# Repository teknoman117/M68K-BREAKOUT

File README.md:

# M68K-BUS-VOLTAGE-CONVERTER

A breakout board for the MC68010 that drops the 5V TTL bus voltages to a 3.3V CMOS bus you can use with an FPGA.

Licensed under CC-BY-SA 4.0

## Pins

All MC68010 signals are converted with the exception of the MC6800 peripheral interface pins. VMA and E are left floating, and VMA is tied to 5V through a 2K2 resistor, which does prevent the use of autovectored interrupts. However, considering it's attached to an FPGA, a proper interrupt controller is a simple thing to add.

The RESET and HALT pins are able to be driven by the M68K itself, or by the FPGA. There are "RESET_OUT" and "HALT_OUT" pins which output the converted state of the pins, and "RESET_IN" and "HALT_IN" which connect to an inverter with open-collector outputs, allowing the FPGA to drive them low.

### Assembled

### PCB

### Schematic

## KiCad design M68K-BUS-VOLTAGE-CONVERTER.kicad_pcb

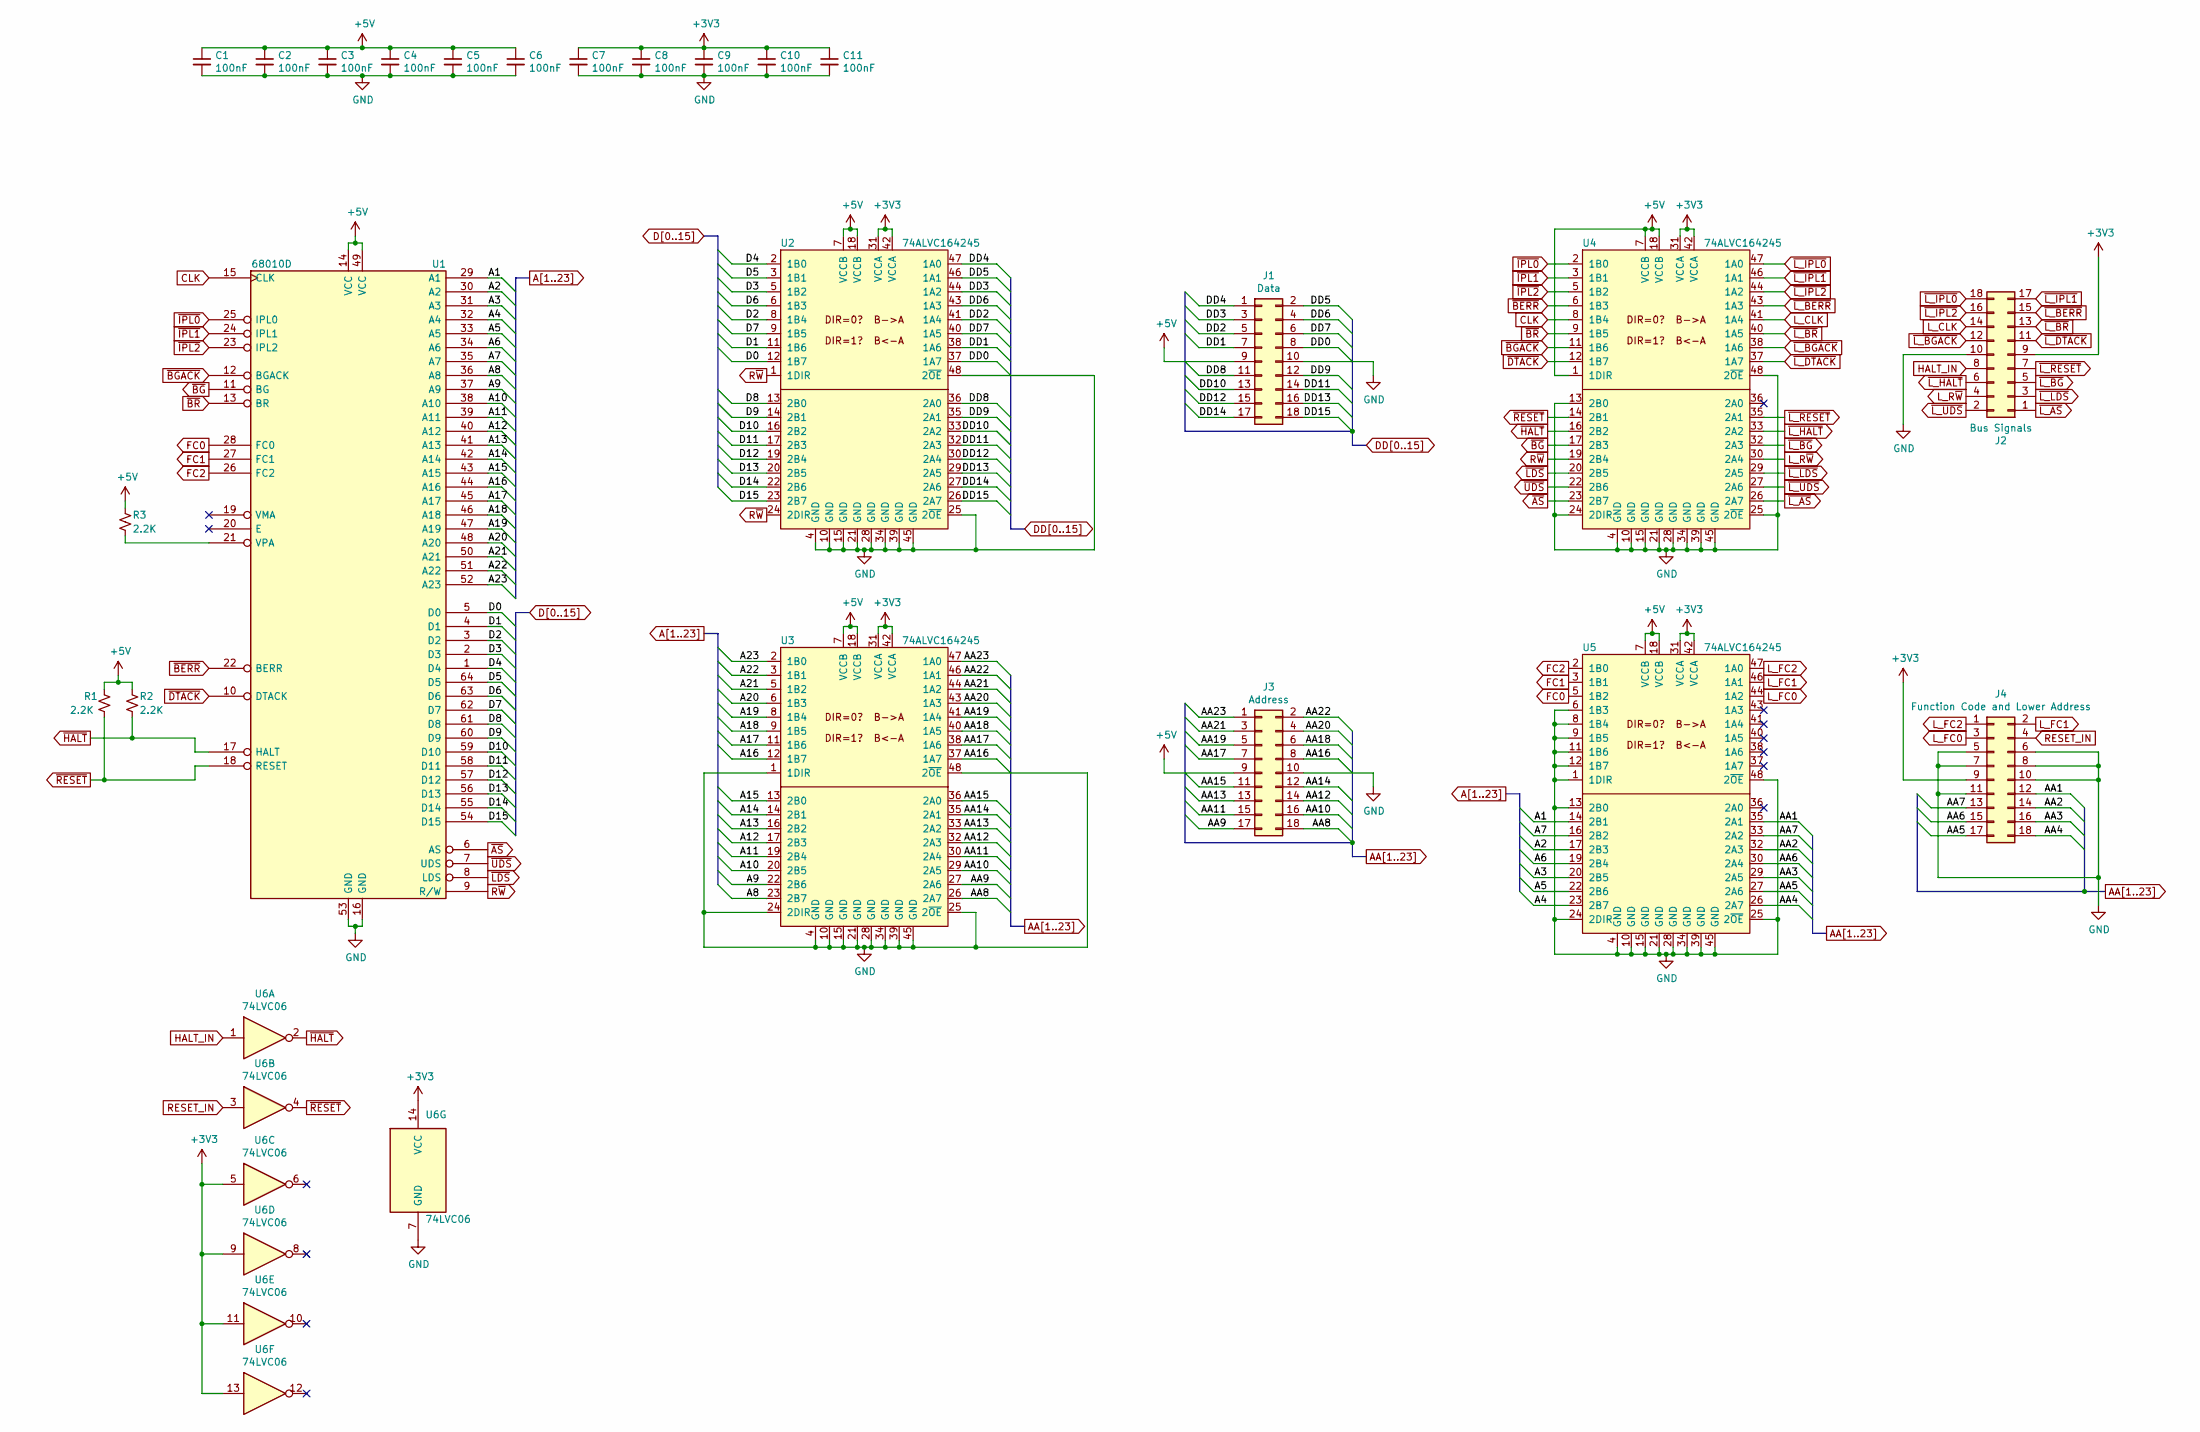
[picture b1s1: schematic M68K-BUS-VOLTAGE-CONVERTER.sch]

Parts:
C1, C2, C3, C4, C5, C6, C7, C8, C9, C10, C11: 100nF; C_0603_1608Metric_Pad1.08x0.95mm_HandSolder
J1: Data; PinHeader_2x09_P2.00mm_Vertical
J2: Bus Signals; PinHeader_2x09_P2.00mm_Vertical
J3: Address; PinHeader_2x09_P2.00mm_Vertical
J4: Function Code and Lower Address; PinHeader_2x09_P2.00mm_Vertical
R1, R2, R3: 2.2K; R_0603_1608Metric_Pad0.98x0.95mm_HandSolder
U1: 68010D; DIP-64_W22.86mm_Socket
U2, U3, U4, U5: 74ALVC164245; TSSOP-48_6.1x12.5mm_P0.5mm
U6: 74LVC06; SOIC-14_3.9x8.7mm_P1.27mm

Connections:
+3V3: C7.1, C8.1, C9.1, C10.1, C11.1, J2.9, J4.9, U2.31 (VCCA), U2.42 (VCCA), U3.31 (VCCA), U3.42 (VCCA), U4.31 (VCCA), U4.42 (VCCA), U5.31 (VCCA), U5.42 (VCCA), U6.5, U6.9, U6.11, U6.13, U6.14 (VCC)
+5V: C1.1, C2.1, C3.1, C4.1, C5.1, C6.1, J1.9, J3.9, R1.1, R2.1, R3.1, U1.14 (VCC), U1.49 (VCC), U2.7 (VCCB), U2.18 (VCCB), U3.7 (VCCB), U3.18 (VCCB), U4.1 (1DIR), U4.7 (VCCB), U4.18 (VCCB), U5.7 (VCCB), U5.18 (VCCB)
A1: U1.29 (A1), U5.14 (2B1)
A2: U1.30 (A2), U5.17 (2B3)
A3: U1.31 (A3), U5.20 (2B5)
A4: U1.32 (A4), U5.23 (2B7)
A5: U1.33 (A5), U5.22 (2B6)
A6: U1.34 (A6), U5.19 (2B4)
A7: U1.35 (A7), U5.16 (2B2)
A8: U1.36 (A8), U3.23 (2B7)
A9: U1.37 (A9), U3.22 (2B6)
A10: U1.38 (A10), U3.20 (2B5)
A11: U1.39 (A11), U3.19 (2B4)
A12: U1.40 (A12), U3.17 (2B3)
A13: U1.41 (A13), U3.16 (2B2)
A14: U1.42 (A14), U3.14 (2B1)
A15: U1.43 (A15), U3.13 (2B0)
A16: U1.44 (A16), U3.12 (1B7)
A17: U1.45 (A17), U3.11 (1B6)
A18: U1.46 (A18), U3.9 (1B5)
A19: U1.47 (A19), U3.8 (1B4)
A20: U1.48 (A20), U3.6 (1B3)
A21: U1.50 (A21), U3.5 (1B2)
A22: U1.51 (A22), U3.3 (1B1)
A23: U1.52 (A23), U3.2 (1B0)
AA1: J4.12, U5.35 (2A1)
AA2: J4.14, U5.32 (2A3)
AA3: J4.16, U5.29 (2A5)
AA4: J4.18, U5.26 (2A7)
AA5: J4.17, U5.27 (2A6)
AA6: J4.15, U5.30 (2A4)
AA7: J4.13, U5.33 (2A2)
AA8: J3.18, U3.26 (2A7)
AA9: J3.17, U3.27 (2A6)
AA10: J3.16, U3.29 (2A5)
AA11: J3.15, U3.30 (2A4)
AA12: J3.14, U3.32 (2A3)
AA13: J3.13, U3.33 (2A2)
AA14: J3.12, U3.35 (2A1)
AA15: J3.11, U3.36 (2A0)
AA16: J3.8, U3.37 (1A7)
AA17: J3.7, U3.38 (1A6)
AA18: J3.6, U3.40 (1A5)
AA19: J3.5, U3.41 (1A4)
AA20: J3.4, U3.43 (1A3)
AA21: J3.3, U3.44 (1A2)
AA22: J3.2, U3.46 (1A1)
AA23: J3.1, U3.47 (1A0)
CLK: U1.15 (CLK), U4.8 (1B4)
D0: U1.5 (D0), U2.12 (1B7)
D1: U1.4 (D1), U2.11 (1B6)
D2: U1.3 (D2), U2.8 (1B4)
D3: U1.2 (D3), U2.5 (1B2)
D4: U1.1 (D4), U2.2 (1B0)
D5: U1.64 (D5), U2.3 (1B1)
D6: U1.63 (D6), U2.6 (1B3)
D7: U1.62 (D7), U2.9 (1B5)
D8: U1.61 (D8), U2.13 (2B0)
D9: U1.60 (D9), U2.14 (2B1)
D10: U1.59 (D10), U2.16 (2B2)
D11: U1.58 (D11), U2.17 (2B3)
D12: U1.57 (D12), U2.19 (2B4)
D13: U1.56 (D13), U2.20 (2B5)
D14: U1.55 (D14), U2.22 (2B6)
D15: U1.54 (D15), U2.23 (2B7)
DD0: J1.8, U2.37 (1A7)
DD1: J1.7, U2.38 (1A6)
DD2: J1.5, U2.41 (1A4)
DD3: J1.3, U2.44 (1A2)
DD4: J1.1, U2.47 (1A0)
DD5: J1.2, U2.46 (1A1)
DD6: J1.4, U2.43 (1A3)
DD7: J1.6, U2.40 (1A5)
DD8: J1.11, U2.36 (2A0)
DD9: J1.12, U2.35 (2A1)
DD10: J1.13, U2.33 (2A2)
DD11: J1.14, U2.32 (2A3)
DD12: J1.15, U2.30 (2A4)
DD13: J1.16, U2.29 (2A5)
DD14: J1.17, U2.27 (2A6)
DD15: J1.18, U2.26 (2A7)
FC0: U1.28 (FC0), U5.5 (1B2)
FC1: U1.27 (FC1), U5.3 (1B1)
FC2: U1.26 (FC2), U5.2 (1B0)
GND: C1.2, C2.2, C3.2, C4.2, C5.2, C6.2, C7.2, C8.2, C9.2, C10.2, C11.2, J1.10, J2.10, J3.10, J4.5, J4.6, J4.7, J4.8, J4.10, J4.11, U1.16 (GND), U1.53 (GND), U2.4 (GND), U2.10 (GND), U2.15 (GND), U2.21 (GND), U2.25 (2~OE), U2.28 (GND), U2.34 (GND), U2.39 (GND), U2.45 (GND), U2.48 (2~OE), U3.1 (1DIR), U3.4 (GND), U3.10 (GND), U3.15 (GND), U3.21 (GND), U3.24 (2DIR), U3.25 (2~OE), U3.28 (GND), U3.34 (GND), U3.39 (GND), U3.45 (GND), U3.48 (2~OE), U4.4 (GND), U4.10 (GND), U4.13 (2B0), U4.15 (GND), U4.21 (GND), U4.24 (2DIR), U4.25 (2~OE), U4.28 (GND), U4.34 (GND), U4.39 (GND), U4.45 (GND), U4.48 (2~OE), U5.1 (1DIR), U5.4 (GND), U5.6 (1B3), U5.8 (1B4), U5.9 (1B5), U5.10 (GND), U5.11 (1B6), U5.12 (1B7), U5.13 (2B0), U5.15 (GND), U5.21 (GND), U5.24 (2DIR), U5.25 (2~OE), U5.28 (GND), U5.34 (GND), U5.39 (GND), U5.45 (GND), U5.48 (2~OE), U6.7 (GND)
HALT_IN: J2.8, U6.1
L_CLK: J2.14, U4.41 (1A4)
L_FC0: J4.3, U5.44 (1A2)
L_FC1: J4.2, U5.46 (1A1)
L_FC2: J4.1, U5.47 (1A0)
L_R~W: J2.4, U4.30 (2A4)
unnamed: R3.2, U1.21 (VPA)
RESET_IN: J4.4, U6.3
R~W: U1.9 (R/W), U2.1 (1DIR), U2.24 (2DIR), U4.19 (2B4)
~AS: U1.6 (AS), U4.23 (2B7)
~BERR: U1.22 (BERR), U4.6 (1B3)
~BG: U1.11 (BG), U4.17 (2B3)
~BGACK: U1.12 (BGACK), U4.11 (1B6)
~BR: U1.13 (BR), U4.9 (1B5)
~DTACK: U1.10 (DTACK), U4.12 (1B7)
~HALT: R2.2, U1.17 (HALT), U4.16 (2B2), U6.2
~IPL0: U1.25 (IPL0), U4.2 (1B0)
~IPL1: U1.24 (IPL1), U4.3 (1B1)
~IPL2: U1.23 (IPL2), U4.5 (1B2)
~LDS: U1.8 (LDS), U4.20 (2B5)
~L_AS: J2.1, U4.26 (2A7)
~L_BERR: J2.15, U4.43 (1A3)
~L_BG: J2.5, U4.32 (2A3)
~L_BGACK: J2.12, U4.38 (1A6)
~L_BR: J2.13, U4.40 (1A5)
~L_DTACK: J2.11, U4.37 (1A7)
~L_HALT: J2.6, U4.33 (2A2)
~L_IPL0: J2.18, U4.47 (1A0)
~L_IPL1: J2.17, U4.46 (1A1)
~L_IPL2: J2.16, U4.44 (1A2)
~L_LDS: J2.3, U4.29 (2A5)
~L_RESET: J2.7, U4.35 (2A1)
~L_UDS: J2.2, U4.27 (2A6)
~RESET: R1.2, U1.18 (RESET), U4.14 (2B1), U6.4
~UDS: U1.7 (UDS), U4.22 (2B6)

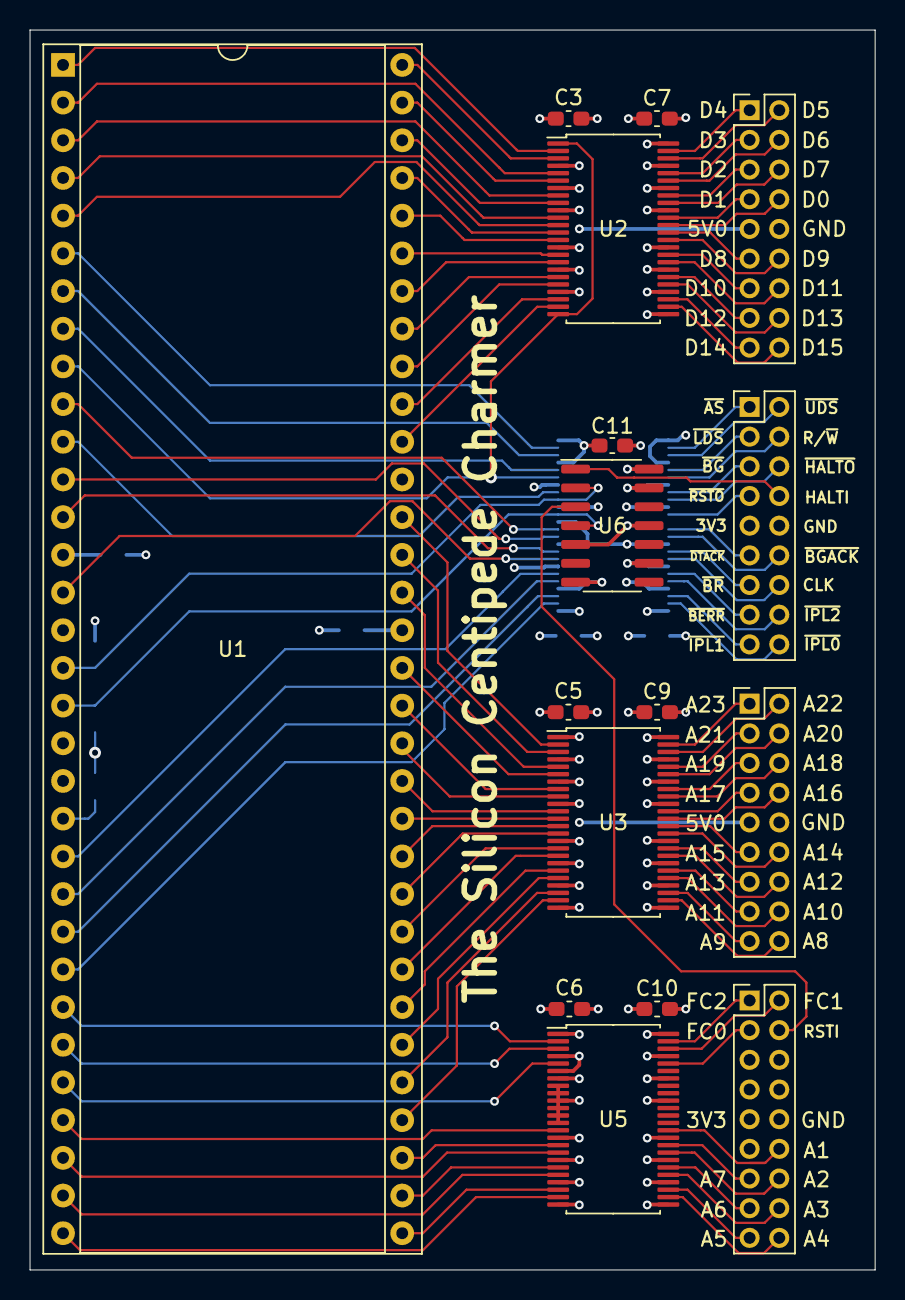
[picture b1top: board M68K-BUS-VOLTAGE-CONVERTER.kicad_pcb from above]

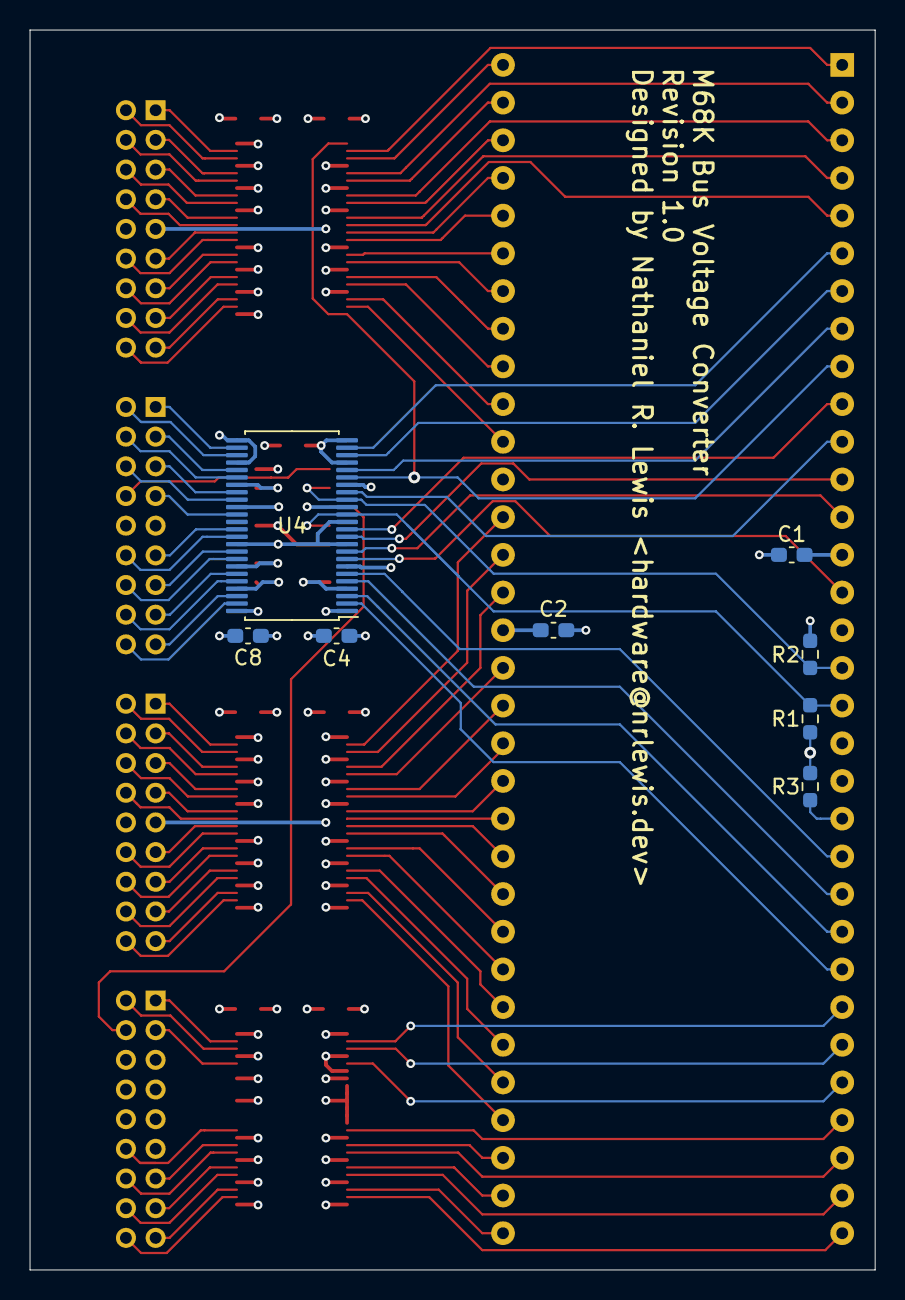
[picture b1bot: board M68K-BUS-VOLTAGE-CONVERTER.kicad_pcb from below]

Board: 4 copper layers, 57.0 x 83.6 mm, 24 parts (8 on the bottom side), 120 nets.

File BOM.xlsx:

Reference | Quantity | Value | Footprint | Datasheet | Link | Mouser_PN
C1 C2 C3 C4 C5 C6 C7 C8 C9 C10 C11 | 11 | 100nF | Capacitor_SMD:C_0603_1608Metric_Pad1.08x0.95mm_HandSolder | https://product.tdk.com/system/files/dam/doc/product/capacit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 | https://www.mouser.com/ProductDetail/810-C1608X7R1E104K | 810-C1608X7R1E104K
J1 J2 J3 J4 | 4 | Conn_02x09_Odd_Even | Connector_PinHeader_2.00mm:PinHeader_2x09_P2.00mm_Vertical |  | https://www.amazon.com/Uxcell-a15062900ux0315-Single-Straigh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
R1 R2 R3 | 3 | 2.2K | Resistor_SMD:R_0603_1608Metric_Pad0.98x0.95mm_HandSolder | https://www.mouser.com/datasheet/2/54/crxxxxx-1858361.pdf | https://www.mouser.com/ProductDetail/Bourns/CR0603-FX-2201EL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 | 652-CR0603FX-2201ELF
U1 | 1 | 68010D | Package_DIP:DIP-64_W22.86mm_Socket | https://www.nxp.com/docs/en/reference-manual/MC68000UM.pdf | https://www.mouser.com/ProductDetail/575-193964 | 575-193964
U2 U3 U4 U5 | 4 | 74ALVC164245 | Package_SO:TSSOP-48_6.1x12.5mm_P0.5mm | https://www.mouser.com/datasheet/2/916/74ALVC164245-1318594.pdf | https://www.mouser.com/ProductDetail/771-74ALVC164245 | 771-74ALVC164245
U6 | 1 | 74LVC06 | Package_SO:SOIC-14_3.9x8.7mm_P1.27mm | https://www.ti.com/lit/ds/symlink/sn74lvc06a.pdf | https://www.mouser.com/ProductDetail/595-SN74LVC06AD | 595-SN74LVC06AD

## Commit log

2021-08-28 first commit (board not complete)
2021-08-30 complete electrical layout for the silicon centipede charmer
2021-08-30 Licensed under CC-BY-SA 4.0
2021-08-30 some trace cleanup, state at manufacturing
2021-09-15 add pictures of assembled board
2021-09-18 rename to M68K-BUS-VOLTAGE-CONVERTER and add schematic
2021-09-18 more pin description
2021-09-18 Added Bill-of-Materials
